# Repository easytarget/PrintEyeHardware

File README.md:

# Depreciated!

RRF 3.5.0 and later no longer support the M408 information fetch command used by PrintEYE

See : https://github.com/easytarget/PrintPy2040
- This is a replacement based on the new ObjectModel data system
- It uses a RP2040 MCU, is smaller, does not need a custom PCB and looks better!

For Posterity: (I am archiving this repo now)

# Duet 'PrintEye' temperature display hardware
## This repository is dedicated to the Hardware used in the printEye; For the full firmware and project description please go to:
## https://github.com/easytarget/PrintEye

This is a low cost and lightweight temperature and status monitor for 3d Printers using Duet (or other repRap Firmware) controllers.

* Atmega328P based
* 2 x 0.96' OLED displays on individual I2C busses
* Level Shifter for Serial connections (duet is 3.3v, 328p is 5v)
* A button
* A LED
* A case
* I include the full KiCad project, exported Gerber Files and more.

PCB Notes:
* The layout is single sided (despite the render above).
  * There are three bridges that need to be placed on the top side.
* Track and pad size+spacing in the PCB layout is pretty generous, but this is a smallish board so some care is needed ;-)
* The FTDI connector needs to be placed on the reverse (copper) side of the PCB.

The included case is designed to have the OLED panels glued in place. The PCB then mounts onto their connectors.
* Glue it lightly! I used generic contact adhesive; this is strong enough but will allow the displays to be gently levered out if needed in the future.
* The case back is a press fit, the plug slot in the back is sized for a dupont connector.
* Fitting and mounting the LED and button I leave up to you.
  * I used thin insulated solid core wires to hold the LED positioned between the two OLED connectors, with a translucent case this is very effective, the LED shines through the lower front of the case itself.
  * The button recess is sized for a 12mm diameter button; glue it in place and then run wires to the PCB. I used a dupont connector here too.

#### Schematic ([Full](./docs/PrintEye-Schematic.pdf))

#### Parts List:

|Ref|Qnty|Value|KiCad Part|Description|
|---|----|-----|----|-----------|
|C1,C2|2|22pF|Device:C|Unpolarized capacitor|
|C5|1|100nF|Device:C|Unpolarized capacitor|
|OLED1,OLED2|2|SSD1315_I2C_OLED|OLED|0.96' OLED I2C display|
|Q1,Q2|2|2N7000|Transistor_FET:2N7000|N-Channel MOSFET, 2.6V Logic Level, TO-92|
|R1,R3,R4,R5|4|10K|Device:R|Resistor|
|R2|1|4K7|Device:R|Resistor|
|R6|1|120R|Device:R|Resistor|
|U1|1|ATmega328-PU|MCU_Microchip_ATmega:ATmega328-PU|20MHz, 32kB Flash, 2kB SRAM, 1kB EEPROM, DIP-28|
|Y1|1|16MHz|Device:Crystal|HC49-4H_Vertical	Two pin crystal|

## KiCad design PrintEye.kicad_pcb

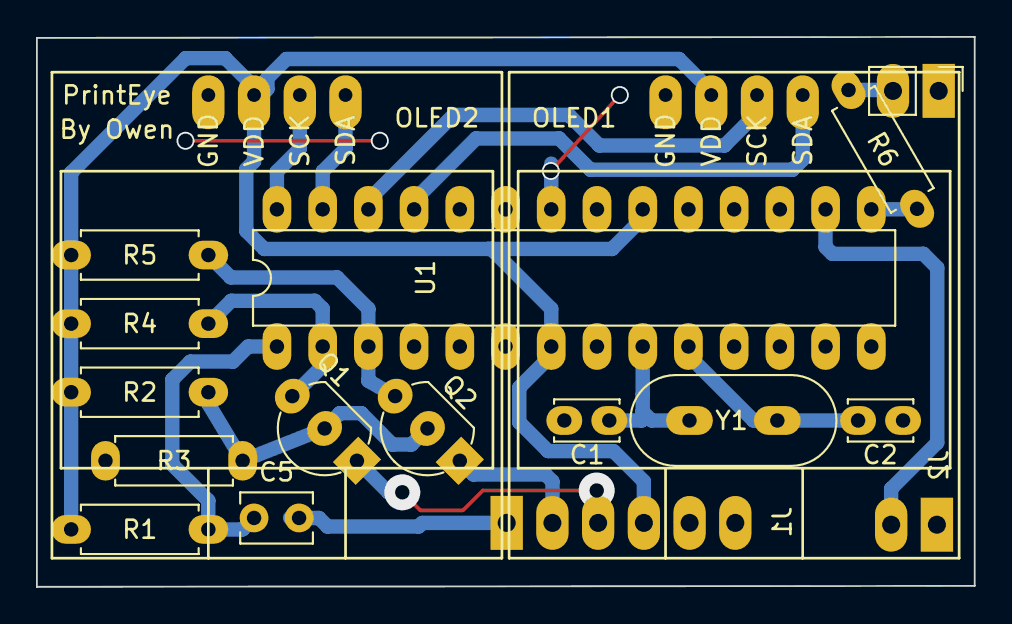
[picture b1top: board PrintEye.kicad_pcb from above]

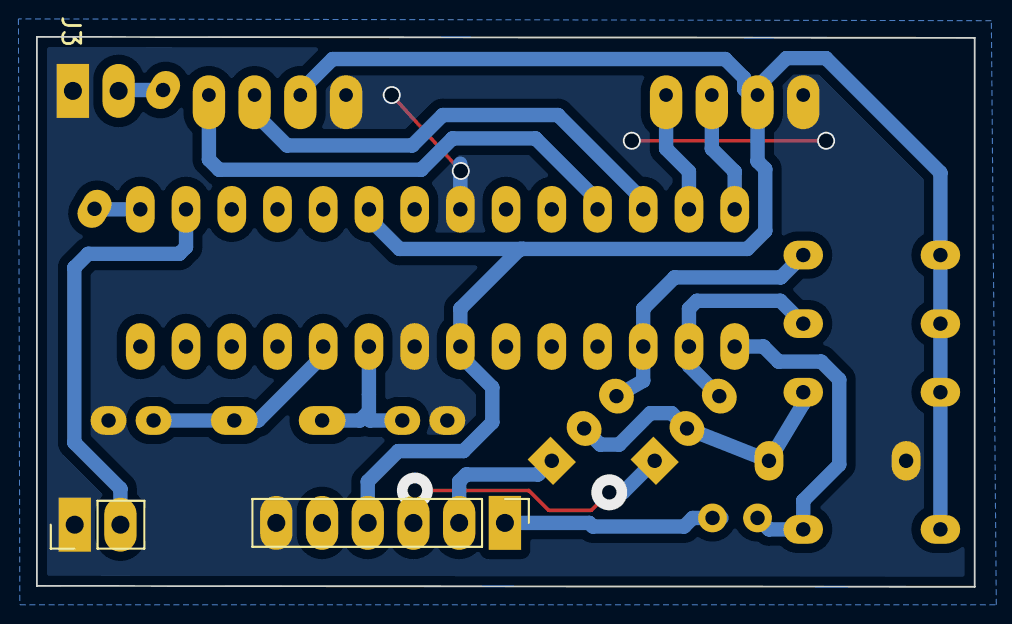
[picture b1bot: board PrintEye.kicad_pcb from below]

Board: 2 copper layers, 52.1 x 30.6 mm, 18 parts (2 on the bottom side), 18 nets.

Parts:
C1, C2: 22pF; C_Disc_D3.4mm_W2.1mm_P2.50mm
C5: 100nF; C_Disc_D3.8mm_W2.6mm_P2.50mm
J1: FTDI; PinHeader_1x06_P2.54mm_Vertical
J2: Pause Button; PinHeader_1x02_P2.54mm_Vertical
J3: Activity LED; PinHeader_1x02_P2.54mm_Vertical
OLED1, OLED2: SSD1315_I2C_OLED; SSD1315-I2C-OLED
Q1, Q2: 2N7000; TO-92_Inline_Wide
R1, R3, R4, R5: 10K; R_Axial_DIN0207_L6.3mm_D2.5mm_P7.62mm_Horizontal
R2: 4K7; R_Axial_DIN0207_L6.3mm_D2.5mm_P7.62mm_Horizontal
R6: 120R; R_Axial_DIN0207_L6.3mm_D2.5mm_P7.62mm_Horizontal
U1: ATmega328-PU; DIP-28_W7.62mm
Y1: 16MHz; Crystal_HC49-4H_Vertical

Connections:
3v3: Q1.2, Q2.2, R2.2, R3.1
5v: J1.4, OLED1.2, OLED2.2, R1.2, R2.1, R4.1, R5.1, U1.7, U1.20
GND: C1.1, C2.1, J1.6, J2.1, J3.1, OLED1.1, OLED2.1, R3.2, U1.8, U1.22
unnamed: C1.2, U1.9, Y1.2
unnamed: C2.2, U1.10, Y1.1
unnamed: C5.1, R1.1, U1.1
unnamed: J2.2, U1.16
unnamed: J3.2, R6.2
unnamed: R6.1, U1.15
RTS: C5.2, J1.1
RX: Q1.3, R4.2, U1.2
RX-3v3: J1.3, Q1.1
SCK1: OLED1.3, U1.26
SCK2: OLED2.3, U1.28
SDA1: OLED1.4, U1.25
SDA2: OLED2.4, U1.27
TX: Q2.3, R5.2, U1.3
TX-3v3: J1.2, Q2.1

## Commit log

2019-06-28 Initial
2019-06-28 Schematic PDF
2019-09-03 Renamed repo, README has some flesh
2019-09-03 Bring up-to-date from my laptop
2019-09-03 Symbol Lib for the OLED
2019-09-03 PCB design and footprints
2019-09-03 Smaller Image
2019-09-03 Add a picture
2019-09-03 Swap TX and RX..
2019-09-03 Move to a bigger connector size
2019-09-04 Documentation; update metadata in Schematic
2019-09-04 Track widths and clearances
2019-09-04 Capacitor ended up joined on PCB, trivial correction to it's pads
2019-09-07 Update with final schematic and pcb revs
2019-09-07 Case Mk1, no base as yet, no button mount either.
2019-09-10 Final Case bits, gerber files.
2019-09-17 Improving documentation for release
2019-09-17 Update README with a BOM etc.
2019-09-17 Updated images
2019-09-17 Intro
2019-09-18 Docs
2019-09-18 More images
2019-09-18 Switch to github
2019-09-18 Notes and queries
2019-09-18 github markup != gitea markup
2019-09-18 more Github markup corrections..
2024-12-21 Reirement Notice
